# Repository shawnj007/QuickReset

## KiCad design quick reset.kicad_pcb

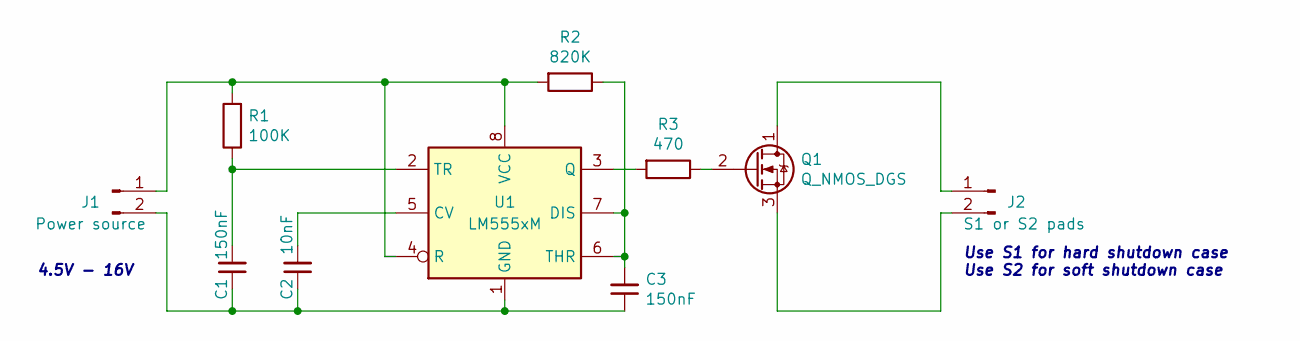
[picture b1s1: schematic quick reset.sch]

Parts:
C1, C3: 150nF; C_Rect_L7.2mm_W4.5mm_P5.00mm_FKS2_FKP2_MKS2_MKP2
C2: 10nF; C_Rect_L4.6mm_W2.0mm_P2.50mm_MKS02_FKP02
J1: Power source; PinHeader_1x02_P2.54mm_Horizontal
J2: S1 or S2 pads; PinHeader_1x02_P2.54mm_Horizontal
Q1: Q_NMOS_DGS; TO-92_Inline_Wide_E-Line
R1: 100K; R_Axial_DIN0204_L3.6mm_D1.6mm_P5.08mm_Horizontal
R2: 820K; R_Axial_DIN0204_L3.6mm_D1.6mm_P5.08mm_Horizontal
R3: 470; R_Axial_DIN0204_L3.6mm_D1.6mm_P5.08mm_Horizontal
U1: LM555xM; DIP-8_W7.62mm_LongPads

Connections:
unnamed: C1.1, C2.1, C3.1, J1.2, U1.1 (GND)
unnamed: C1.2, R1.1, U1.2 (TR)
unnamed: C2.2, U1.5 (CV)
unnamed: C3.2, R2.1, U1.6 (THR), U1.7 (DIS)
unnamed: J1.1, R1.2, R2.2, U1.4 (R), U1.8 (VCC)
unnamed: J2.1, Q1.1 (D)
unnamed: J2.2, Q1.3 (S)
unnamed: Q1.2 (G), R3.1
unnamed: R3.2, U1.3 (Q)

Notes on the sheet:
Use S1 for hard shutdown case Use S2 for soft shutdown case
4.5V - 16V

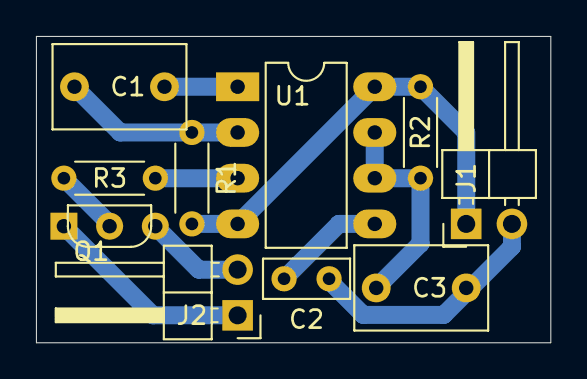
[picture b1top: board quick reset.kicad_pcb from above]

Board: 2 copper layers, 28.6 x 17.0 mm, 10 parts (0 on the bottom side), 9 nets.

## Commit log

2020-11-15 Add png's and read_sensor.py
